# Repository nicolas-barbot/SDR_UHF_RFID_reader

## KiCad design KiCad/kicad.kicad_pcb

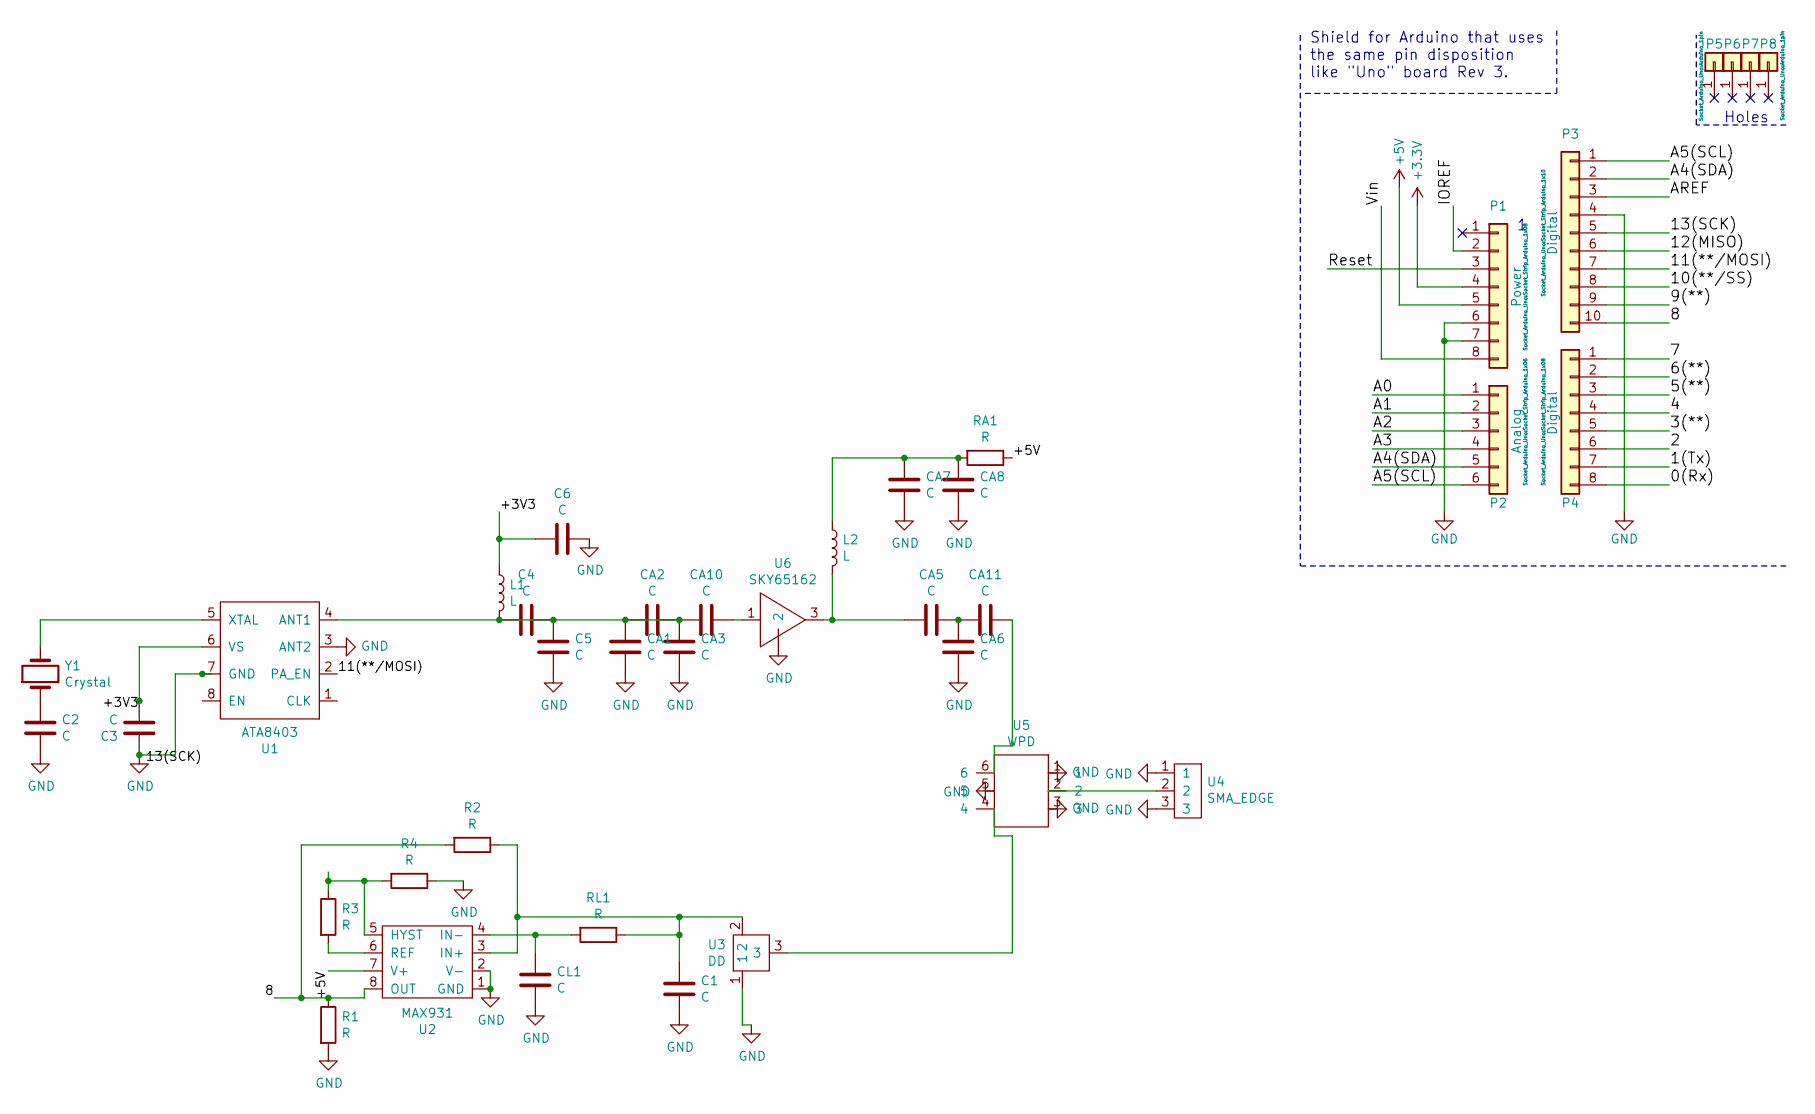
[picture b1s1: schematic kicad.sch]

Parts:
C1, C2, C3, C4, C5, C6: C; C_0805_2012Metric
CA1, CA2, CA3, CA5, CA6, CA7, CA8, CA10, CA11: C; C_0805_2012Metric
CL1: C; C_0805_2012Metric
L1, L2: L; L_0805_2012Metric
P1: Power; Socket_Strip_Arduino_1x08
P2: Analog; Socket_Strip_Arduino_1x06
P3: Digital; Socket_Strip_Arduino_1x10
P4: Digital; Socket_Strip_Arduino_1x08
P5, P6, P7, P8: CONN_01X01; Arduino_1pin
R1, R2, R3, R4: R; R_0805_2012Metric
RA1: R; R_0805_2012Metric
RL1: R; R_0805_2012Metric
U1: ATA8403; TSSOP-8_3x3mm_P0.65mm
U2: MAX931; SOIC-8
U3: DD; SOT-23
U4: SMA_EDGE
U5: WPD; SOT-23-6
U6: SKY65162
Y1: Crystal; Crystal_SMD_HC49-SD

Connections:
+5V: P1.5, RA1.1, U2.7 (V+)
/0(Rx): P4.8
/1(Tx): P4.7
/2: P4.6
/3(**): P4.5
/4: P4.4
/5(**): P4.3
/6(**): P4.2
/7: P4.1
/8: P3.10, R1.1, R2.2, U2.8 (OUT)
/9(**): P3.9
/10(**/SS): P3.8
/11(**/MOSI): P3.7, U1.2 (PA_EN)
/12(MISO): P3.6
/13(SCK): P3.5, U1.8 (EN)
/A0: P2.1
/A1: P2.2
/A2: P2.3
/A3: P2.4
/A4(SDA): P2.5, P3.2
/A5(SCL): P2.6, P3.1
/AREF: P3.3
/IOREF: P1.2
/Reset: P1.3
/Vin: P1.8
GND: C1.2, C2.2, C3.1, C5.2, C6.1, CA1.2, CA3.2, CA6.2, CA7.2, CA8.2, CL1.2, P1.6, P1.7, P3.4, R1.2, R4.1, U1.3 (ANT2), U1.7 (GND), U2.1 (GND), U2.2 (V-), U3.1, U4.1, U4.3, U5.1, U5.3, U5.5, U6.~ (2)
unnamed: C1.1, R2.1, RL1.1, U2.3 (IN+), U3.2
unnamed: C2.1, Y1.1
unnamed: CA5.2, L2.2, U6.3
unnamed: CA7.1, CA8.1, L2.1, RA1.2
unnamed: CA10.1, U6.1
unnamed: CA11.1, U5.6
unnamed: CA5.1, CA6.1, CA11.2
unnamed: CL1.1, RL1.2, U2.4 (IN-)
unnamed: R3.1, R4.2, U2.5 (HYST)
unnamed: R3.2, U2.6 (REF)
unnamed: U1.5 (XTAL), Y1.2
unnamed: U3.3, U5.4
unnamed: U4.2, U5.2

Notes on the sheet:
Holes
Shield for Arduino that uses the same pin disposition like "Uno" board Rev 3.

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
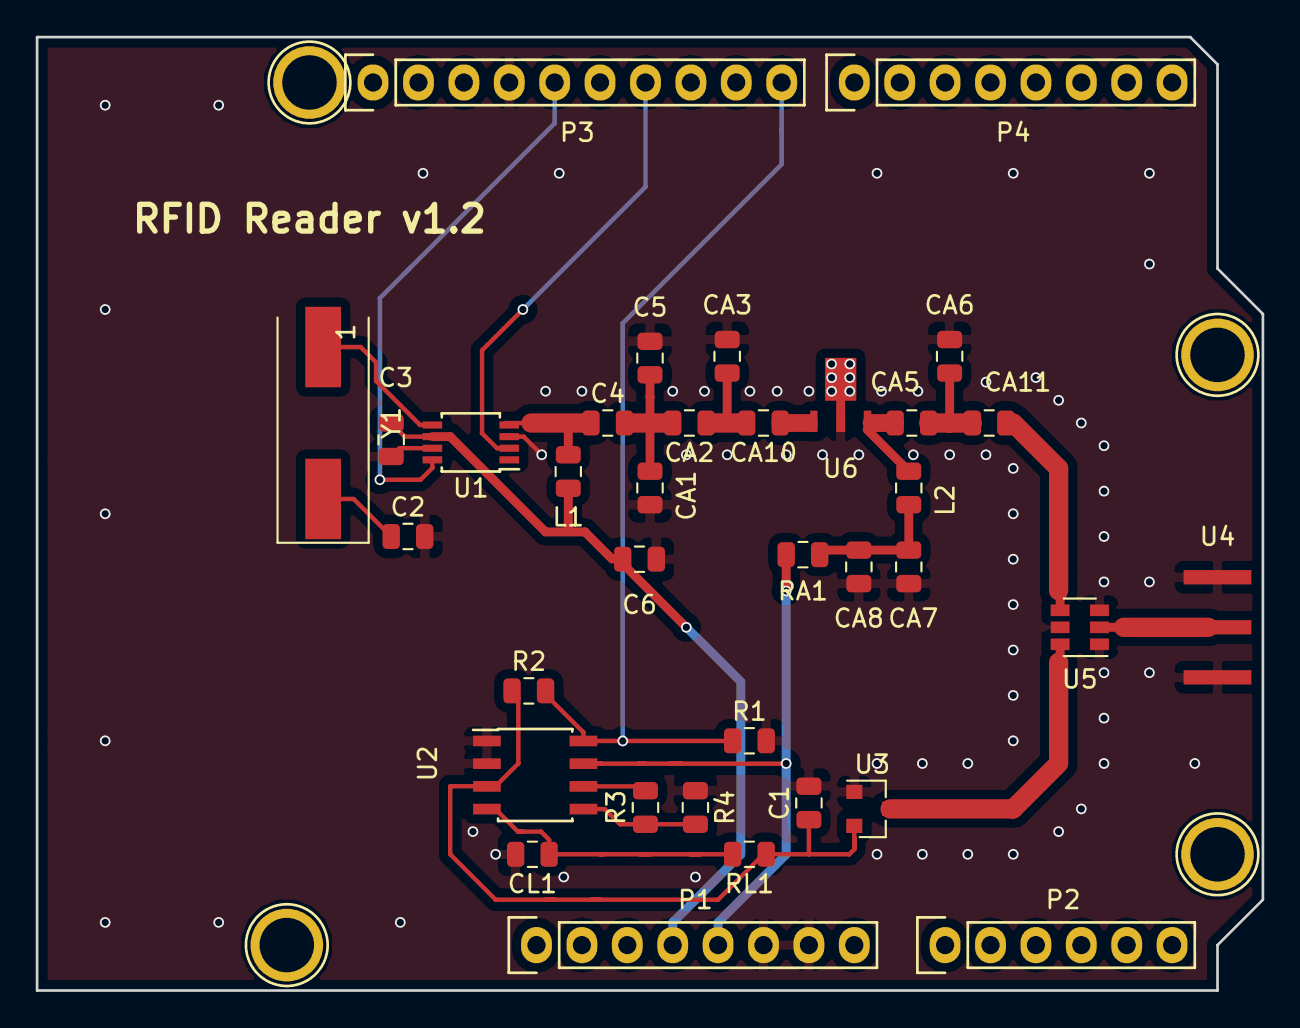
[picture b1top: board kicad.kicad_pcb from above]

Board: 2 copper layers, 68.6 x 53.3 mm, 39 parts (0 on the bottom side), 24 nets.

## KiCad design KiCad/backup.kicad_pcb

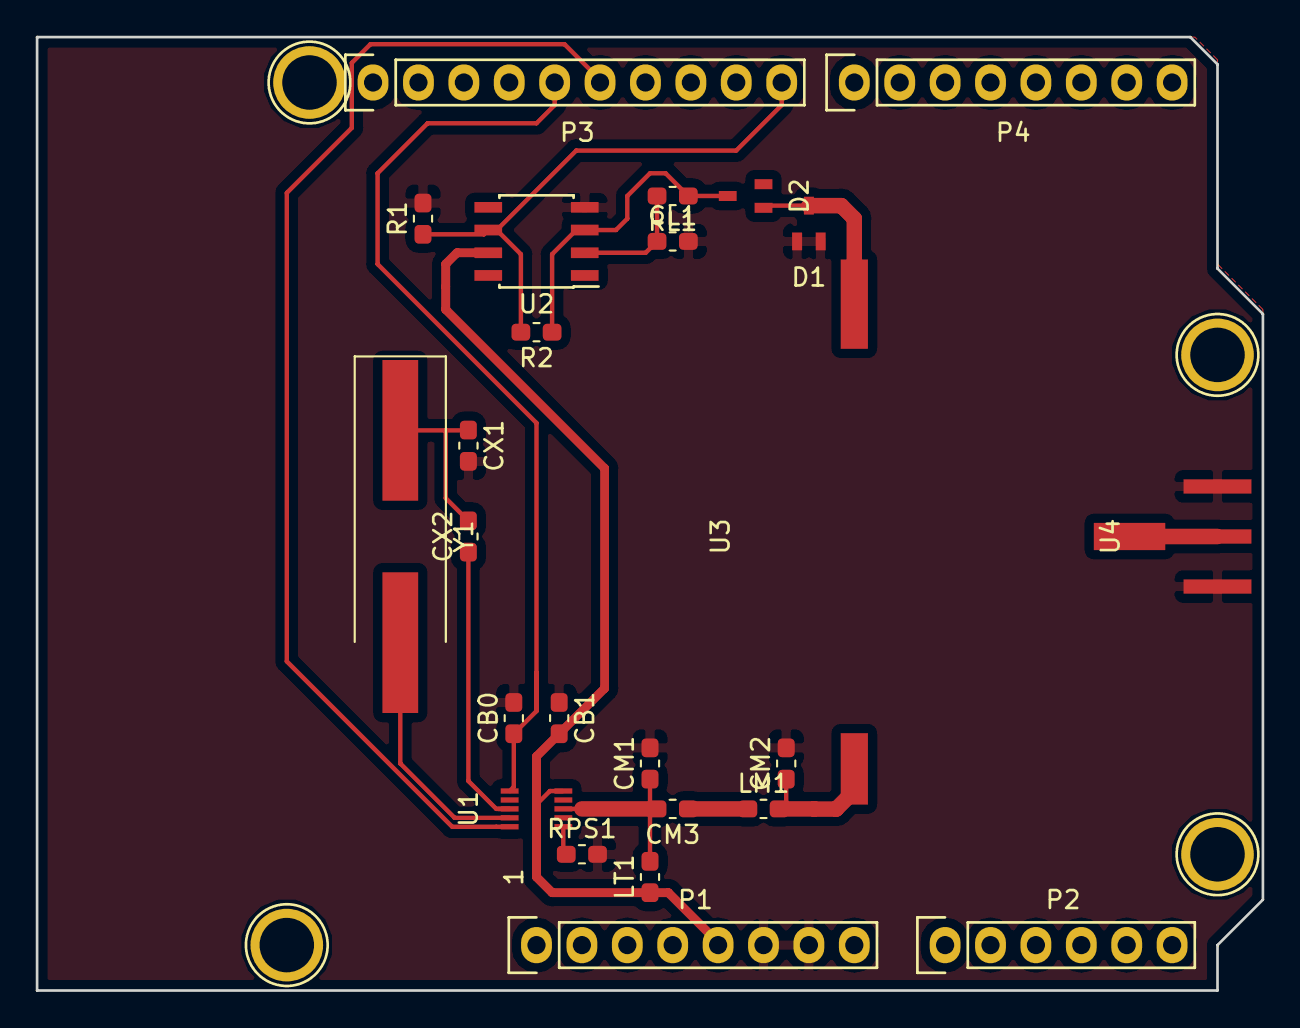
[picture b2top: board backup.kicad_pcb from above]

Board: 2 copper layers, 68.6 x 53.3 mm, 29 parts (0 on the bottom side), 18 nets.

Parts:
CB0, CB1: C; C_0603_1608Metric_Pad1.05x0.95mm_HandSolder
CL1: C; C_0603_1608Metric_Pad1.05x0.95mm_HandSolder
CM1, CM2, CM3: C; C_0603_1608Metric_Pad1.05x0.95mm_HandSolder
CX1, CX2: C; C_0603_1608Metric_Pad1.05x0.95mm_HandSolder
D1, D2: D; SOT-323
LM1: L; L_0603_1608Metric_Pad1.05x0.95mm_HandSolder
LT1: L; L_0603_1608Metric_Pad1.05x0.95mm_HandSolder
P1: Power; Socket_Strip_Arduino_1x08
P2: Analog; Socket_Strip_Arduino_1x06
P3: Digital; Socket_Strip_Arduino_1x10
P4: Digital; Socket_Strip_Arduino_1x08
P5, P6, P7, P8: CONN_01X01; Arduino_1pin
R1, R2: R; R_0603_1608Metric_Pad1.05x0.95mm_HandSolder
RL1: R; R_0603_1608Metric_Pad1.05x0.95mm_HandSolder
RPS1: R; R_0603_1608Metric_Pad1.05x0.95mm_HandSolder
U1: TH72035; 10L QFN 3x3 Dual
U2: OP179GS; SOIC-8_3.9x4.9mm_P1.27mm
U3: cicrulator; circulator
U4: SMA_EDGE
Y1: Crystal; Crystal_SMD_HC49-SD_HandSoldering

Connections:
+5V: CB1.2, LT1.1, P1.5, U1.10, U2.7
/8: P3.10, R1.1, R2.2, U2.6
/12(MISO): P3.6, U1.5
/13(SCK): CB0.1, P3.5, U1.1
/A4(SDA): P2.5, P3.2
/A5(SCL): P2.6, P3.1
GND: CB0.2, CB1.1, CL1.2, CM1.2, CM2.2, CX1.2, D1.1, D1.3, P1.6, P1.7, P3.4, R1.2, RPS1.2, U1.7, U1.9, U2.4, U4.2, U4.3
unnamed: CL1.1, RL1.2, U2.2
unnamed: CM1.1, CM3.2, LT1.2, U1.8
unnamed: CM2.1, LM1.2, U3.1
unnamed: CM3.1, LM1.1
unnamed: CX1.1, CX2.2, Y1.1
unnamed: CX2.1, U1.3
unnamed: D1.2, D2.1, U3.2
unnamed: D2.2, R2.1, RL1.1, U2.3
unnamed: RPS1.1, U1.6
unnamed: U1.4, Y1.2
unnamed: U3.3, U4.1
